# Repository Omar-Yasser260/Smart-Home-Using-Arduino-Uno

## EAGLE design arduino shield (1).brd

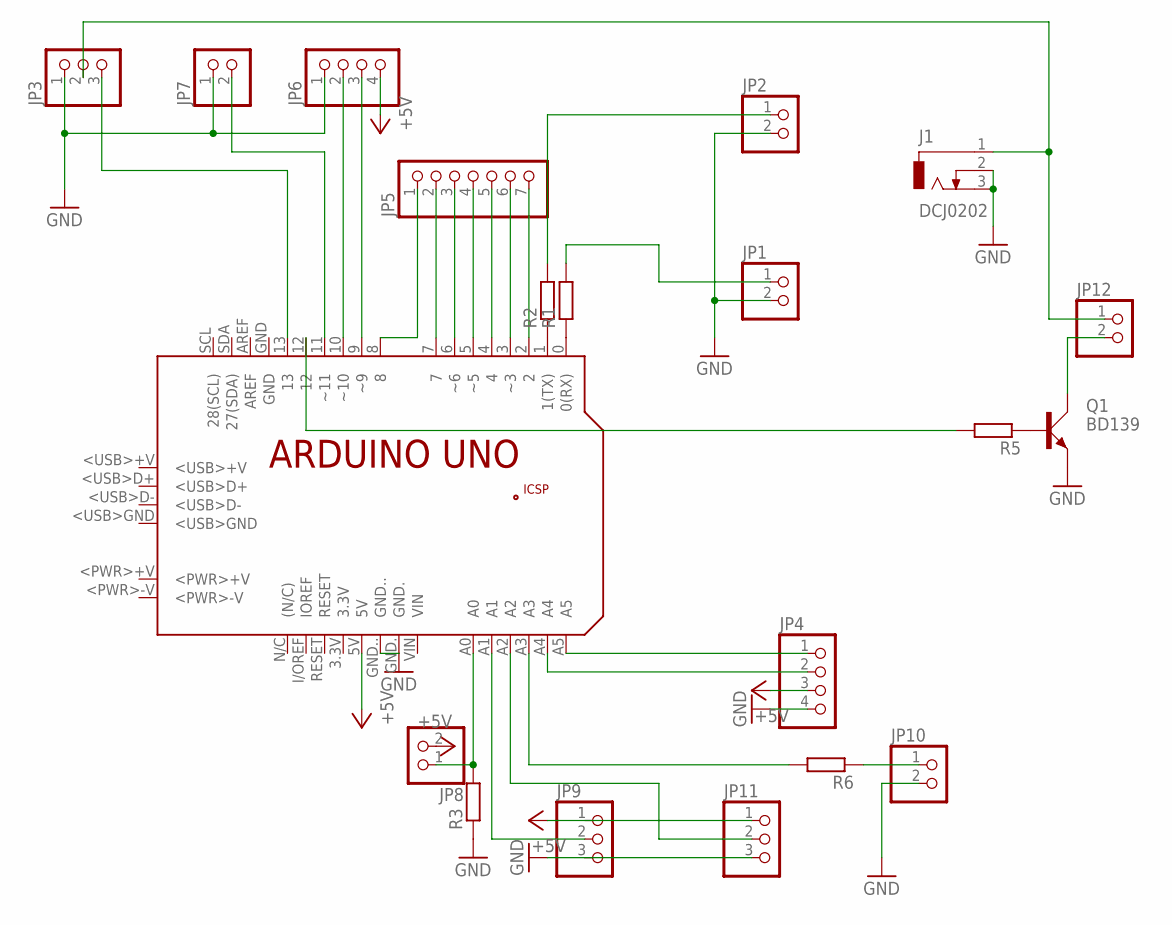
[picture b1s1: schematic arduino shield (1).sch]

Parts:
J1: DCJ0202
JP1, JP2, JP7, JP8, JP10, JP12: PINHD-1X2; 1X02
JP3, JP9, JP11: PINHD-1X3; 1X03
JP4, JP6: PINHD-1X4; 1X04
JP5: PINHD-1X7; 1X07
PCB1: ARDUINO_UNO
Q1: BD139; TO126AV
R1, R2, R3, R5, R6: R-EU_0207/7; 0207/7

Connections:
+5V: JP4.3, JP6.4, JP8.2, JP9.1, JP11.1, PCB1.5V
GND: J1.2, J1.3, JP1.2, JP2.2, JP3.1, JP4.4, JP6.1, JP7.1, JP9.3, JP10.2, JP11.3, PCB1.GND., PCB1.GND.., Q1.E, R3.1
unnamed: PCB1.0 (0(RX)), R1.1
unnamed: PCB1.1 (1(TX)), R2.1
unnamed: JP5.7, PCB1.2
unnamed: JP5.6, PCB1.3 (~3)
unnamed: JP5.5, PCB1.4
unnamed: JP5.4, PCB1.5 (~5)
unnamed: JP5.3, PCB1.6 (~6)
unnamed: JP5.2, PCB1.7
unnamed: JP5.1, PCB1.8
unnamed: JP1.1, R1.2
unnamed: JP2.1, R2.2
unnamed: JP10.1, R6.1
unnamed: JP6.3, PCB1.9 (~9)
unnamed: JP6.2, PCB1.10 (~10)
unnamed: JP7.2, PCB1.11 (~11)
unnamed: JP3.3, PCB1.13
unnamed: J1.1, JP3.2, JP12.1
unnamed: JP8.1, PCB1.A0, R3.2
unnamed: JP4.1, PCB1.A5
unnamed: JP4.2, PCB1.A4
unnamed: JP9.2, PCB1.A1
unnamed: PCB1.A3, R6.2
unnamed: JP11.2, PCB1.A2
unnamed: Q1.B, R5.1
unnamed: JP12.2, Q1.C
unnamed: PCB1.12, R5.2

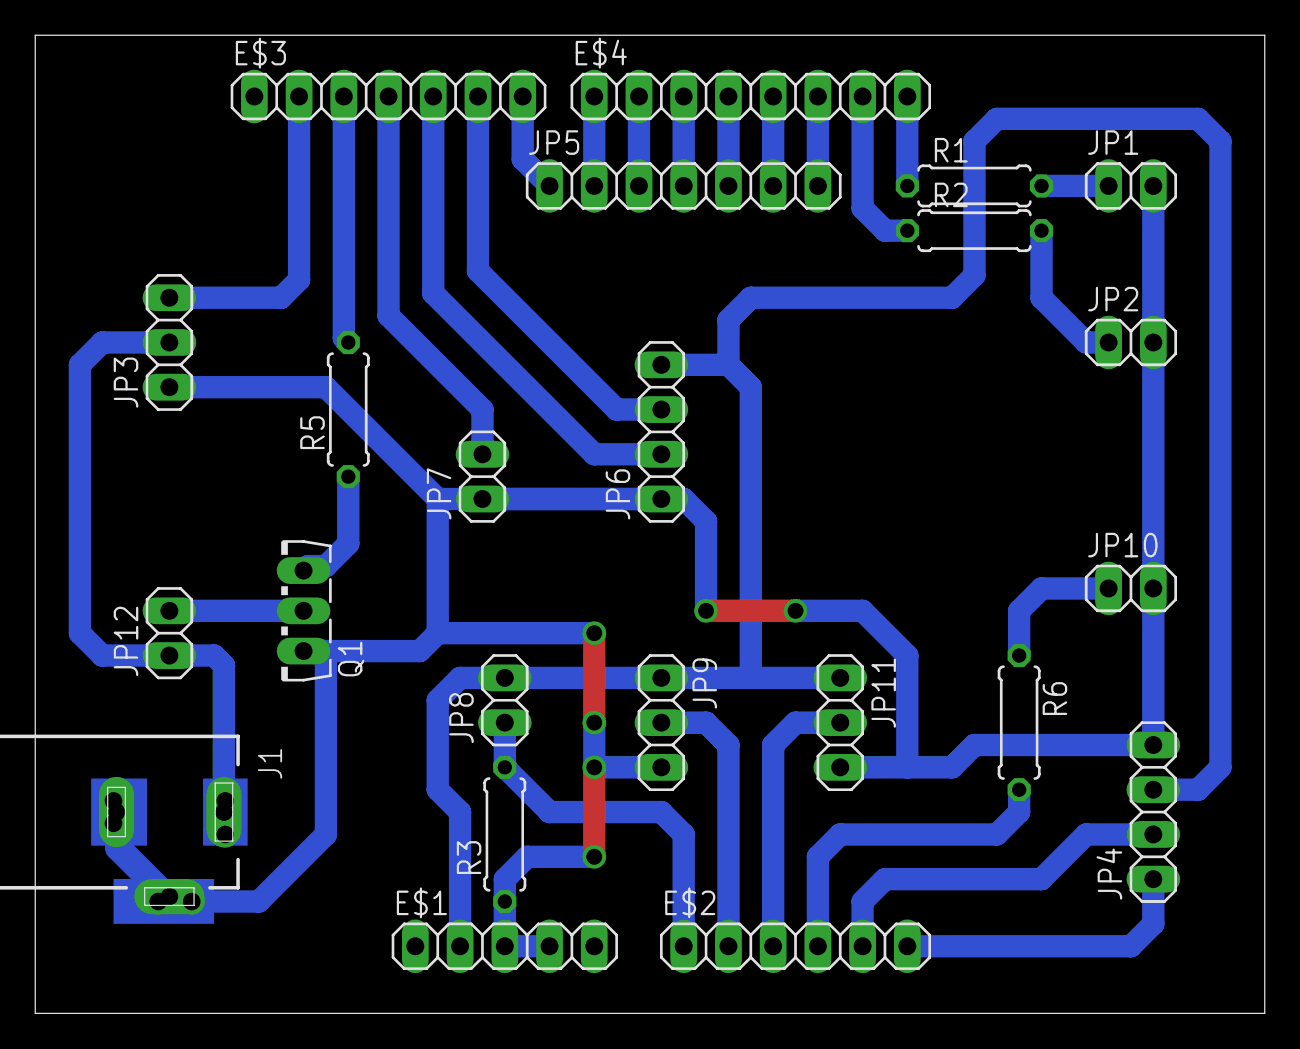
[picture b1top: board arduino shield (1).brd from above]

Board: 2 copper layers, 69.8 x 55.5 mm, 23 parts (0 on the bottom side), 9 nets.

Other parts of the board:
E$1: 1X05
E$2: 1X06
E$3: 1X07
E$4: 1X08
